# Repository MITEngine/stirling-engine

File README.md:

# stirling-engine
Stirling Engine Tachometer

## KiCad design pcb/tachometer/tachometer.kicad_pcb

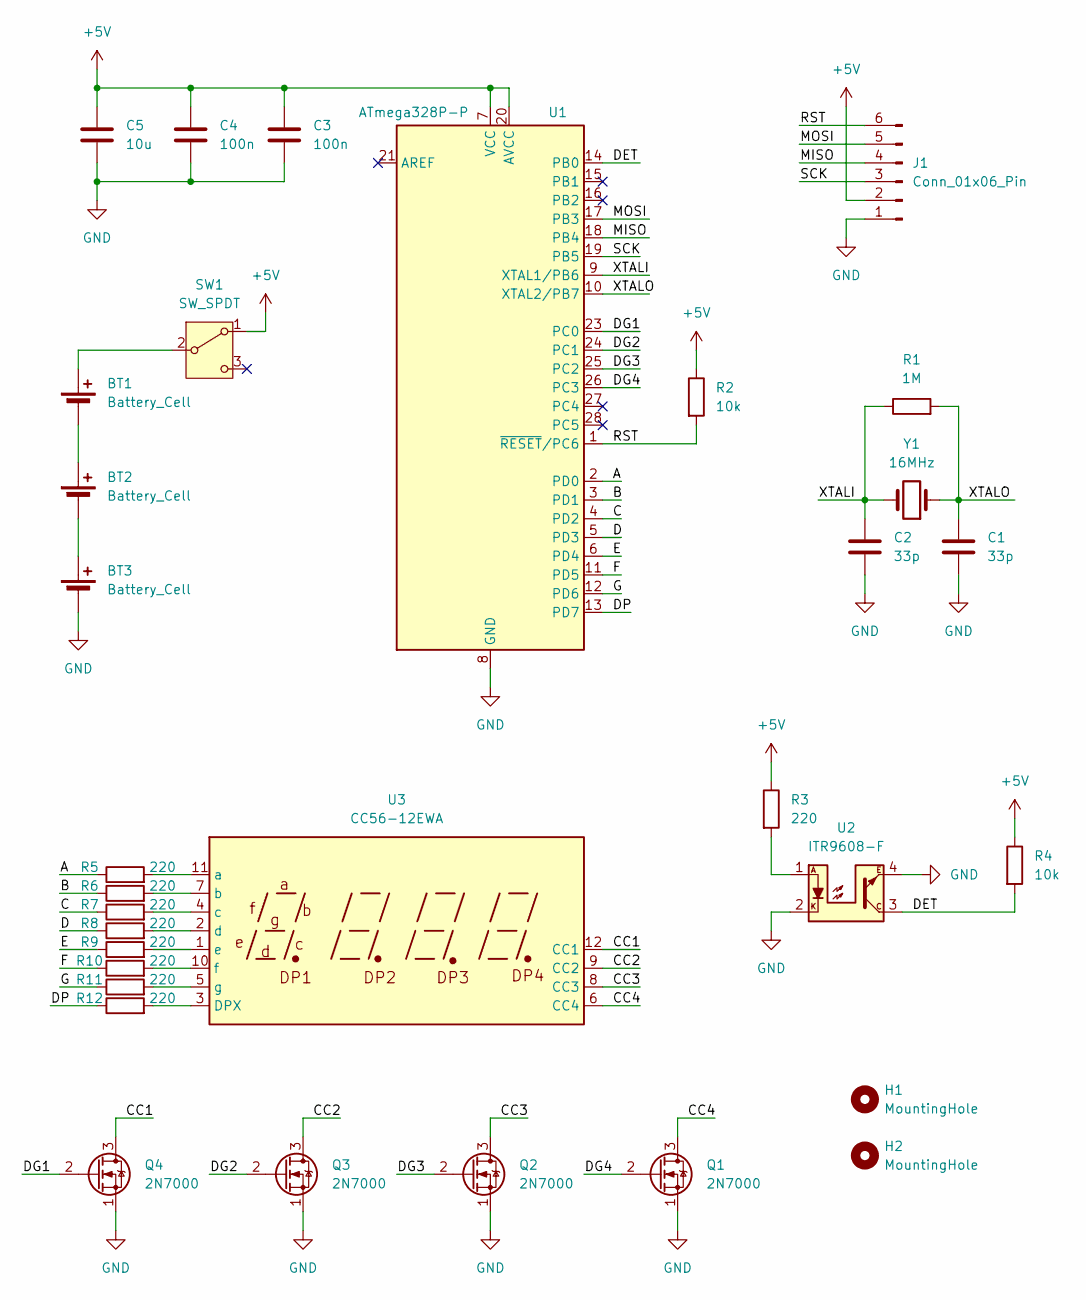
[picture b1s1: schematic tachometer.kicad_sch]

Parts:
BT1, BT2, BT3: Battery_Cell; BH-AAA-A1AJ001; LCSC C5290189
C1, C2: 33p; C_Disc_D3.8mm_W2.6mm_P2.50mm; LCSC C2170185
C3, C4: 100n; C_Disc_D4.7mm_W2.5mm_P5.00mm; LCSC C5632426
C5: 10u; C_Disc_D5.1mm_W3.2mm_P5.00mm; LCSC C2761733
H1, H2: MountingHole; MountingHole_3.2mm_M3
J1: Conn_01x06_Pin; PinHeader_1x06_P2.54mm_Vertical; LCSC C240305
Q1, Q2, Q3, Q4: 2N7000; TO-92_Inline; LCSC C9114
R1: 1M; R_Axial_DIN0207_L6.3mm_D2.5mm_P7.62mm_Horizontal; LCSC C2903250
R2, R4: 10k; R_Axial_DIN0207_L6.3mm_D2.5mm_P7.62mm_Horizontal; LCSC C410695
R3, R5, R6, R7, R8, R9, R10, R11, R12: 220; R_Axial_DIN0207_L6.3mm_D2.5mm_P7.62mm_Horizontal; LCSC C57439
SW1: SW_SPDT; SW_Slide_SPDT_Straight_CK_OS102011MS2Q; LCSC C136719
U1: ATmega328P-P; DIP-28_W7.62mm; LCSC C33901
U2: ITR9608-F; Everlight_ITR9608-F; LCSC C3656393
U3: CC56-12EWA; CA56-12EWA; LCSC C54396
Y1: 16MHz; Crystal_HC49-4H_Vertical; LCSC C16212

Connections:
+5V: C3.1, C4.1, C5.1, J1.2, R2.1, R3.1, R4.1, SW1.1 (A), U1.7 (VCC), U1.20 (AVCC)
/A: R5.1, U1.2 (PD0)
/B: R6.1, U1.3 (PD1)
/C: R7.1, U1.4 (PD2)
/CC1: Q4.3 (D), U3.12 (CC1)
/CC2: Q3.3 (D), U3.9 (CC2)
/CC3: Q2.3 (D), U3.8 (CC3)
/CC4: Q1.3 (D), U3.6 (CC4)
/D: R8.1, U1.5 (PD3)
/DET: R4.2, U1.14 (PB0), U2.3
/DG1: Q4.2 (G), U1.23 (PC0)
/DG2: Q3.2 (G), U1.24 (PC1)
/DG3: Q2.2 (G), U1.25 (PC2)
/DG4: Q1.2 (G), U1.26 (PC3)
/DP: R12.1, U1.13 (PD7)
/E: R9.1, U1.6 (PD4)
/F: R10.1, U1.11 (PD5)
/G: R11.1, U1.12 (PD6)
/MISO: J1.4, U1.18 (PB4)
/MOSI: J1.5, U1.17 (PB3)
/RST: J1.6, R2.2, U1.1 (~RESET/PC6)
/SCK: J1.3, U1.19 (PB5)
/XTALI: C2.2, R1.1, U1.9 (XTAL1/PB6), Y1.2
/XTALO: C1.2, R1.2, U1.10 (XTAL2/PB7), Y1.1
GND: BT3.2 (-), C1.1, C2.1, C3.2, C4.2, C5.2, J1.1, Q1.1 (S), Q2.1 (S), Q3.1 (S), Q4.1 (S), U1.8 (GND), U1.22 (GND), U2.2, U2.4
unnamed: BT1.1 (+), SW1.2 (B)
unnamed: BT1.2 (-), BT2.1 (+)
unnamed: BT2.2 (-), BT3.1 (+)
unnamed: R3.2, U2.1
unnamed: R12.2, U3.3 (DPX)
unnamed: R5.2, U3.11 (a)
unnamed: R6.2, U3.7 (b)
unnamed: R7.2, U3.4 (c)
unnamed: R8.2, U3.2 (d)
unnamed: R9.2, U3.1 (e)
unnamed: R10.2, U3.10 (f)
unnamed: R11.2, U3.5 (g)

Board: 2 copper layers, 32 parts (1 on the bottom side), 37 nets, no tracks yet.

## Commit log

2024-09-08 Finish schematic and component layout
